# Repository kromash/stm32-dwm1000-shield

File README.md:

# Arduino Nano (Nucleo-32) DWM1000 Shield
Arduino Nano compatible shield with DWM1000 module. KiCAD project ready for order in JLCPCB.  

Shield uses only 12 from 15 pins on each side. I tested it with my Nucleo-32 (STM32G431).

# 3D View

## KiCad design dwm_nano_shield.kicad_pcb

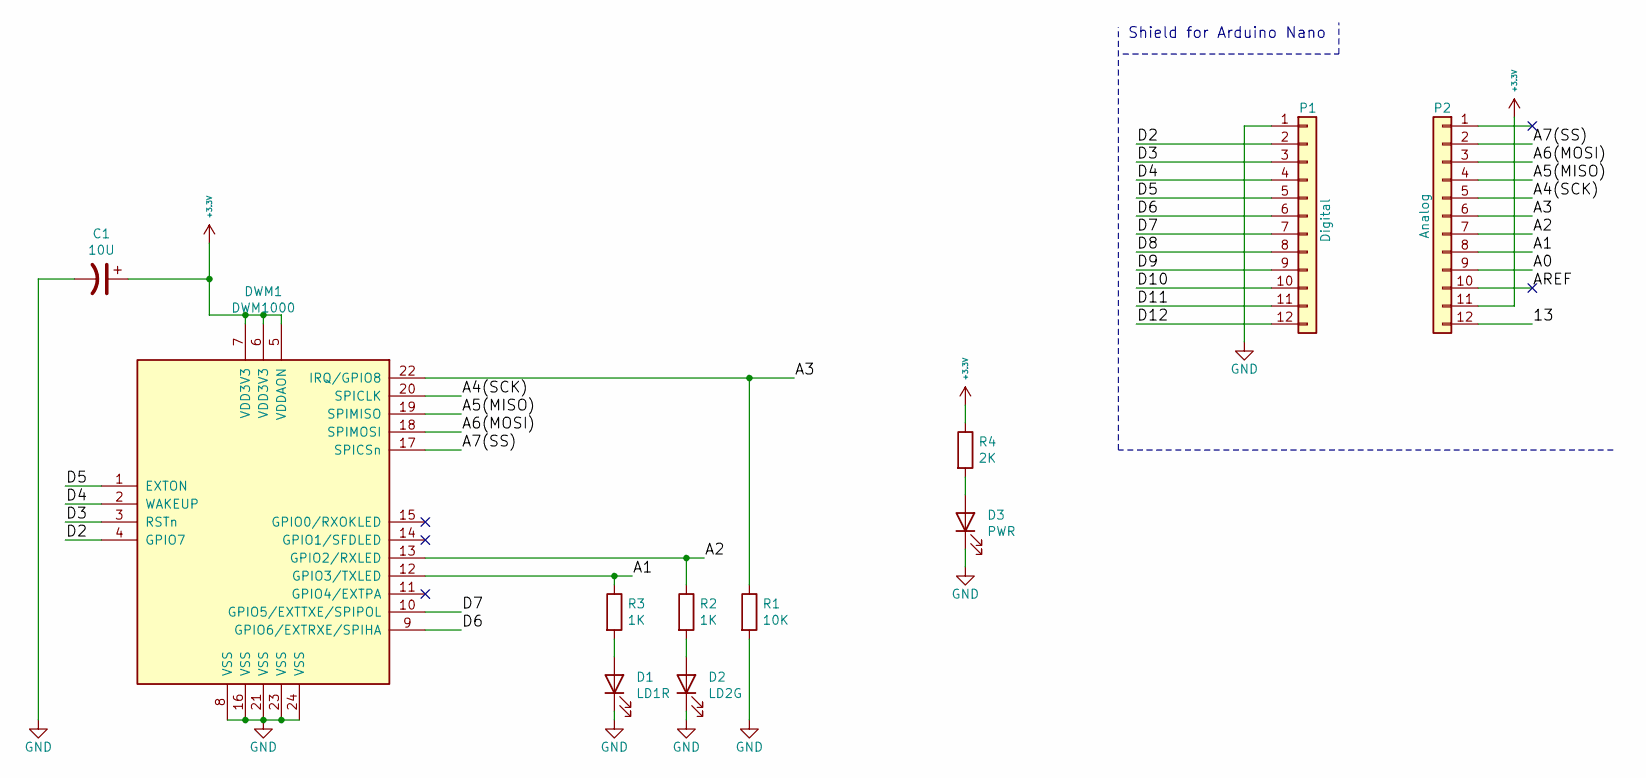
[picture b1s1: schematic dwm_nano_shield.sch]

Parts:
C1: 10U; C_0603_1608Metric
D1: LD1R; LED_0603_1608Metric
D2: LD2G; LED_0603_1608Metric
D3: PWR; LED_0603_1608Metric
DWM1: DWM1000
P1: Digital; PinSocket_1x12_P2.54mm_Vertical
P2: Analog; PinSocket_1x12_P2.54mm_Vertical
R1: 10K; R_0603_1608Metric
R2, R3: 1K; R_0603_1608Metric
R4: 2K; R_0603_1608Metric

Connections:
+3V3: C1.1, DWM1.5 (VDDAON), DWM1.6 (VDD3V3), DWM1.7 (VDD3V3), P2.11, R4.1
/13: P2.12
/A0: P2.9
/A1: DWM1.12 (GPIO3/TXLED), P2.8, R3.1
/A2: DWM1.13 (GPIO2/RXLED), P2.7, R2.1
/A3: DWM1.22 (IRQ/GPIO8), P2.6, R1.1
/A4(SCK): DWM1.20 (SPICLK), P2.5
/A5(MISO): DWM1.19 (SPIMISO), P2.4
/A6(MOSI): DWM1.18 (SPIMOSI), P2.3
/A7(SS): DWM1.17 (SPICSn), P2.2
/AREF: P2.10
/D2: DWM1.4 (GPIO7), P1.2
/D3: DWM1.3 (RSTn), P1.3
/D4: DWM1.2 (WAKEUP), P1.4
/D5: DWM1.1 (EXTON), P1.5
/D6: DWM1.9 (GPIO6/EXTRXE/SPIHA), P1.6
/D7: DWM1.10 (GPIO5/EXTTXE/SPIPOL), P1.7
/D8: P1.8
/D9: P1.9
/D10: P1.10
/D11: P1.11
/D12: P1.12
GND: C1.2, D1.1 (K), D2.1 (K), D3.1 (K), DWM1.8 (VSS), DWM1.16 (VSS), DWM1.21 (VSS), DWM1.23 (VSS), DWM1.24 (VSS), P1.1, R1.2
unnamed: D1.2 (A), R3.2
unnamed: D2.2 (A), R2.2
unnamed: D3.2 (A), R4.2

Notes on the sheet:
Shield for Arduino Nano

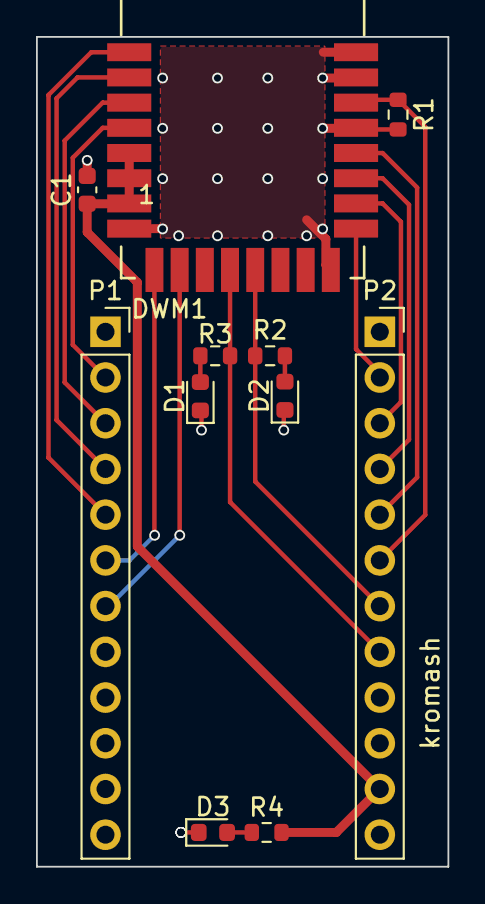
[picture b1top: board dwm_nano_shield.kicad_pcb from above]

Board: 2 copper layers, 22.9 x 46.1 mm, 11 parts (0 on the bottom side), 18 nets.

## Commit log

2021-09-14 Main KiCad files
2021-09-14 Add 3D shield image
